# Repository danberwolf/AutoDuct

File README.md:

# AutoDuct: smart motorized air duct shutter

AutoDuct is a smart DIY air duct shutter for decentralized ventilation systems in residential buildings. Its main purpose is to automatically control airflow and block outside noise using a 3D-printed shutter system. This solves the problem of unintended air flow into the apartment during cold and windy days to increase comfort, maintain energy efficiency and reduce expenses for heating.
The integrated electronics of the air duct shutter assembly also gives full control of the ventilation system’s fan to enable features like flexible ventilation schedules and automatic humidity control. The Bluetooth low energy interface lets you control and configure the system via a mobile app. Multiple ventilation units can also be integrated into Apple HomeKit via a simple ESP32-powered BLE-to-Wifi-bridge.

# Mechanical Assembly

At the heart of this device is a mostly 3D-printed linear actuator which is used to open and close a shutter disc to prevent unwanted airflow. The 3D-printed leadscrew of the actuator is directly attached to a small brushed DC motor with an integrated gearbox.

Integrated into the encapsulated actuator unit two hall effect switches on a separate ring-shaped PCB are used to detect the end stop positions (open/close) of the shutter mechanism in combination with tiny magnets. The axial position of these magnets can be adjusted to compensate for mechanical tolerances in the assembly.

Note: the actuator unit does not use any additional (ball) bearings to keep the BOM simple and material cost low. Axial and radial forces are solely absorbed by the 3D-printed linear guides and the integrated bearings of the geared motor. This could potentially reduce longevity of the assembly but has not been an issue while testing multiple units over more than a year now. Use of silicone grease is highly recommended.

# Electronics

The electronics are based around a Microchip 32-bit microcontroller (PIC32MX), which might be a little bit overpowered for this project but was available from a previous project and has a neat footprint. The +3V3 rail is generated from the +12V bus by a step-down converter. The geared DC motor is driven by a dedicated H-bridge driver IC (DRV8801).

Behind the front cover of the assembly another small PCB is hidden. This PCB contains the Bluetooth low energy module (HM-17), a serial EEPROM, a real time clock (RTC) IC and a humidity and temperature sensor. User feedback is given via a white LED which shines through the 3D-printed enclosure and has brightness control via PWM.

# Firmware

The main processor of the device (PIC32MX150F128B) runs a super simple multitasking OS which takes care of these main tasks:

* monitoring of fan control PWM signal from the stock ventilation system control bus
* reading of temperature / humidity from SHT31 sensor
* generating the PWM control signal for connected fan
* motor control including end stop detection
* handle the BLE communication when the system is connected to the mobile app 

Depending on the selected operating mode, the device will perform the following actions:

* opening / closing the valve based on the detected fan control PWM signal
* automatically activating the fan based on schedule events or humidity thresholds
* react to remote control commands issued via the mobile app / BLE connection 

A custom bootloader was developed which enables over-the-air firmware updates via the Bluetooth low energy interface. 

# Project Video

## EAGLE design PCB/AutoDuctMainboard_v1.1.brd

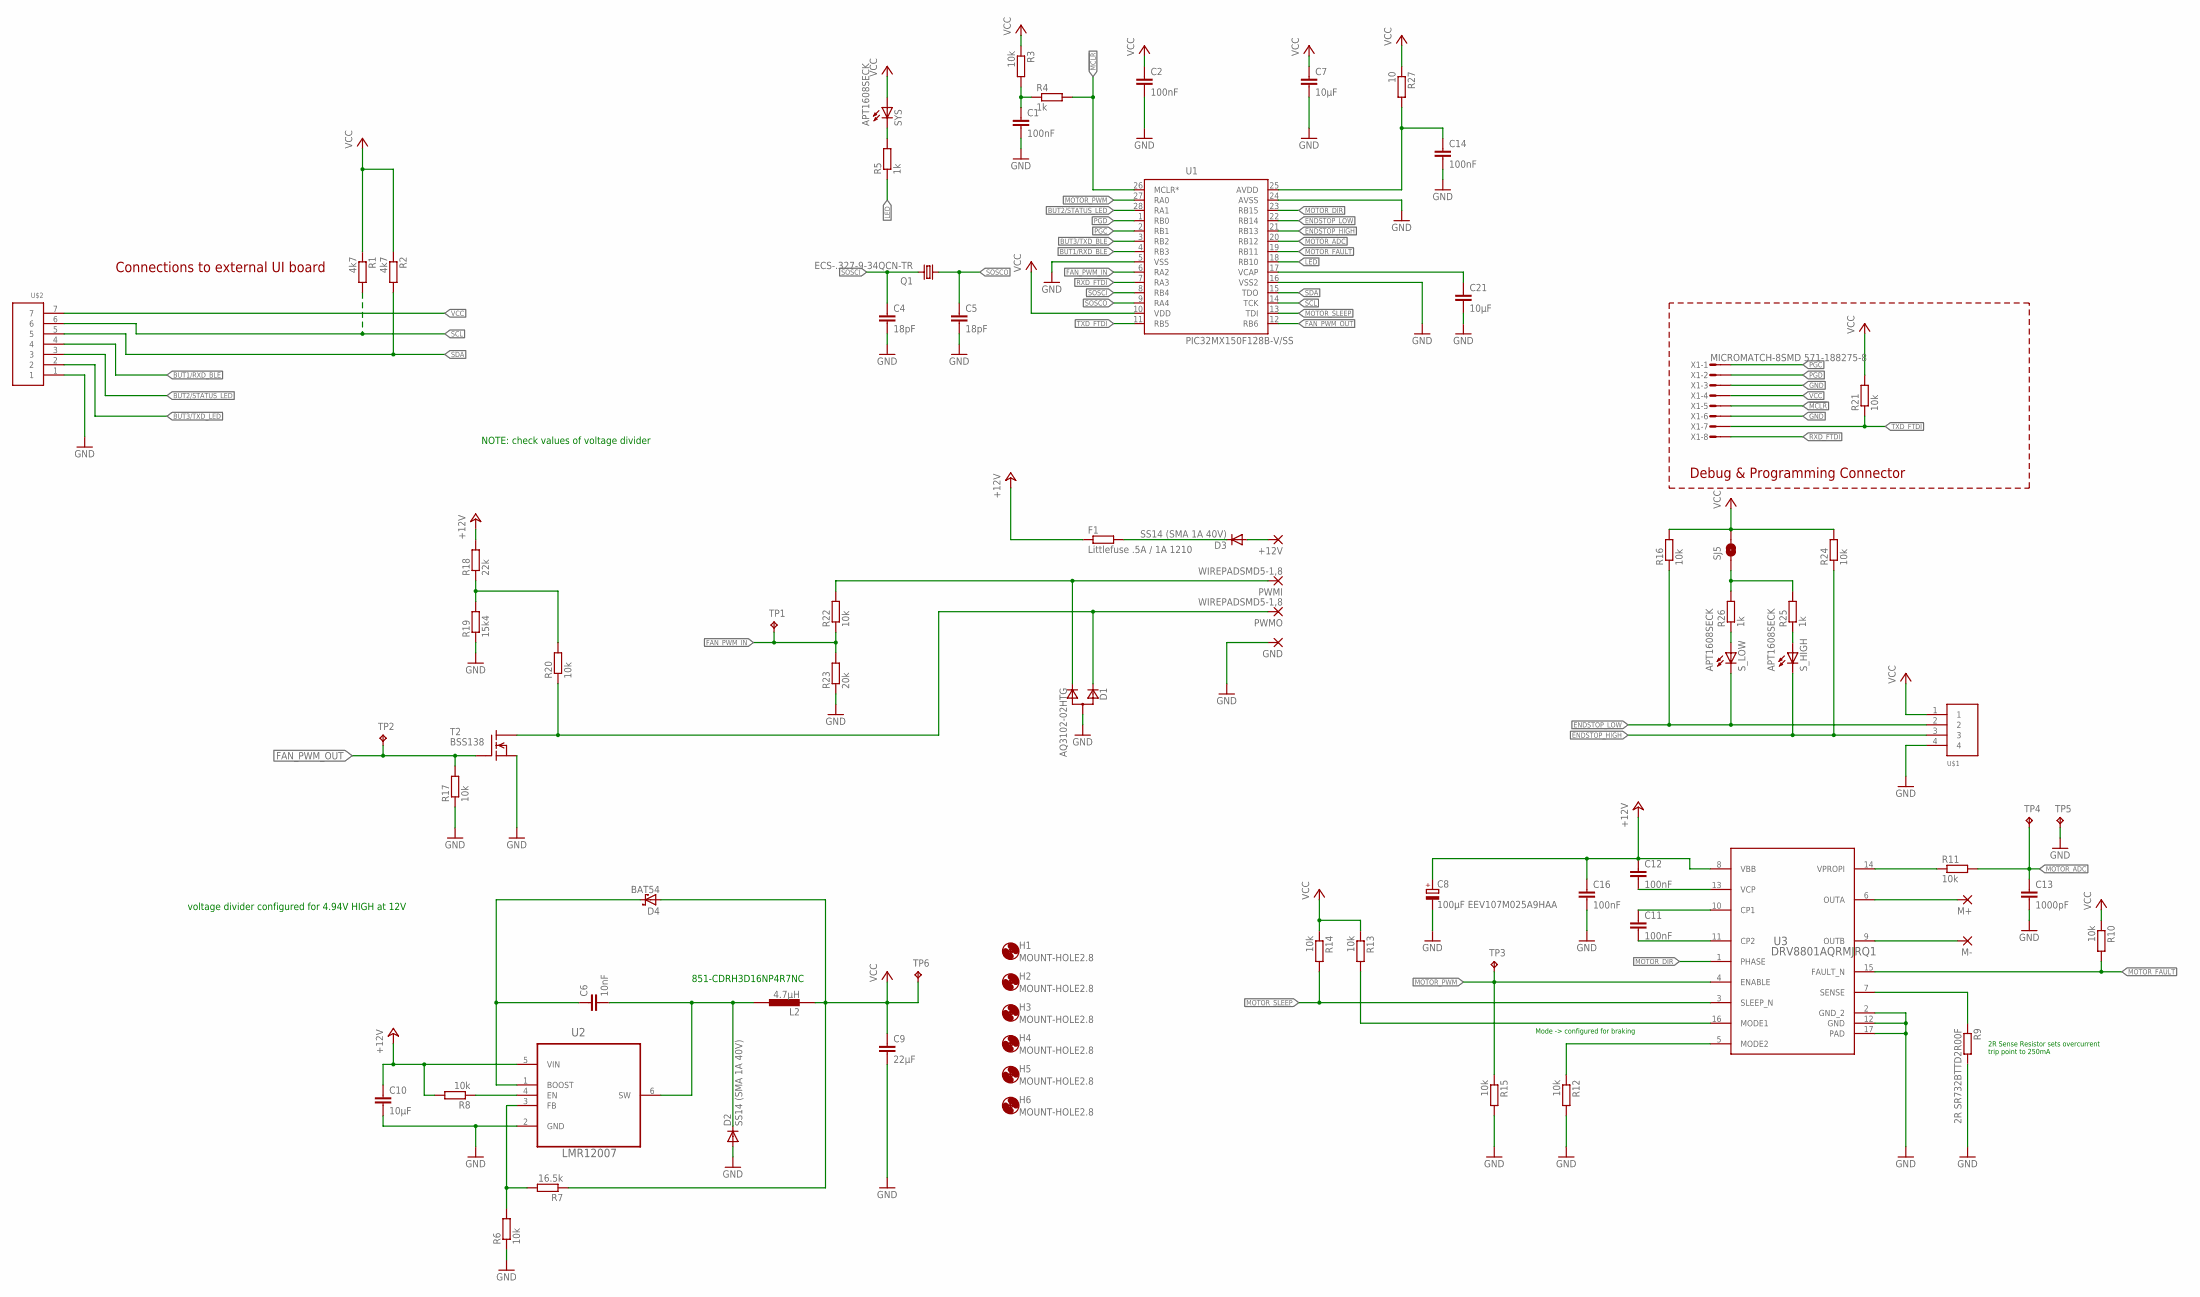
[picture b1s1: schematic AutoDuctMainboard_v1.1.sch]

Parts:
+12V: SMD5; SMD2,54-5,08
C1, C2, C11, C12, C14: 100nF; C0402
C4, C5: 18pF; C0603K
C6: 10nF; C0603K
C7, C21: 10µF; C0603K
C8: 100µF EEV107M025A9HAA; 153CLV-0605
C9: 22µF; C0805K
C10: 10µF; C1206K
C13: 1000pF; C0603K
C16: 100nF; C0603K
D1: AQ3102-02HTG; SOT323
D2, D3: SS14 (SMA 1A 40V); DO214AC
D4: BAT54; SOT23
F1: Littlefuse .5A / 1A 1210; R1210
GND: SMD5; SMD2,54-5,08
H1, H2, H3, H4, H5, H6: MOUNT-HOLE2.8; 2,8
L2: 4.7µH; CDRH3D16; MOUSER CDRH3D16/LDNP-4R7NC
M+: SMD5; SMD2,54-5,08
M-: SMD5; SMD2,54-5,08
PWMI: WIREPADSMD5-1,8; 5-1,8
PWMO: WIREPADSMD5-1,8; 5-1,8
Q1: ECS-.327-9-34QCN-TR; 3.2X1.5
R1, R2: 4k7; R0603
R3, R6, R8, R10, R11, R12, R13, R14, R15, R16, R17, R20, R21, R22, R24: 10k; R0603
R4, R5, R25, R26: 1k; R0603
R7: 16.5k; R0603
R9: 2R SR732BTTD2R00F; R1206
R18: 22k; R0603
R19: 15k4; R0603
R23: 20k; R0603
R27: 10; R0603
SJ5: RXLED; SJ_2S-NO
SYS: APT1608SECK; CHIPLED_0603
S_HIGH: APT1608SECK; CHIPLED_0603
S_LOW: APT1608SECK; CHIPLED_0603
T2: BSS138; SOT23
TP1, TP2, TP3, TP6: TPTP13R; TP13R
TP4: TPTP09R; TP09R
TP5: TPTP12SQ; TP12SQ
U1: PIC32MX150F128B-V/SS; QFN65P600X600X100-29N
U2: LMR12007; SOT95P285X100-6N
U3: DRV8801AQRMJRQ1; RMJ0016A
U$1: WIREPAD1X4
U$2: WIREPAD1X7
X1: MICROMATCH-8SMD 571-188275-8; MICROMATCH-8-SMD

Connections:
!MCLR: R4.2, U1.26 (MCLR*), X1.5
+12V: C8.+, C10.1, C12.1, C16.1, F1.1, R8.2, R18.2, U2.5 (VIN), U3.8 (VBB)
BUT1/RXD_BLE: U1.4 (RB3), U$2.4
BUT2/STATUS_LED: U1.28 (RA1), U$2.3
BUT3/TXD_BLE: U1.3 (RB2)
BUT3/TXD_LED: U$2.2
ENDSTOP_HIGH: R24.1, S_HIGH.C, U1.21 (RB13), U$1.3
ENDSTOP_LOW: R16.1, S_LOW.C, U1.22 (RB14), U$1.2
FAN_PWM_IN: R22.1, R23.2, TP1.TP, U1.6 (RA2)
FAN_PWM_IN_RAW: D1.3 (C2), PWMI.1, R22.2
FAN_PWM_OUT: R17.2, T2.1 (G), TP2.TP, U1.12 (RB6)
FAN_PWM_OUT_SHIFTED: D1.2 (C1), PWMO.1, R20.1, T2.3 (D)
GND: C1.2, C2.2, C4.2, C5.2, C7.2, C8.-, C9.2, C10.2, C13.2, C14.2, C16.2, C21.2, D1.1 (A), D2.A, GND.1, R6.1, R9.2, R12.2, R15.2, R17.1, R19.1, R23.1, T2.2 (S), TP5.TP, U1.5 (VSS), U1.16 (VSS2), U1.24 (AVSS), U2.2 (GND), U3.2 (GND_2), U3.12 (GND), U3.17 (PAD), U$1.4, U$2.1, X1.3, X1.6
LED: R5.1, U1.18 (RB10)
MOTOR+: M+.1, U3.6 (OUTA)
MOTOR-: M-.1, U3.9 (OUTB)
MOTOR_ADC: C13.1, R11.2, TP4.TP, U1.20 (RB12)
MOTOR_DIR: U1.23 (RB15), U3.1 (PHASE)
MOTOR_FAULT: R10.2, U1.19 (RB11), U3.15 (FAULT_N)
MOTOR_PWM: R15.1, TP3.TP, U1.27 (RA0), U3.4 (ENABLE)
MOTOR_SLEEP: R14.2, U1.13 (TDI), U3.3 (SLEEP_N)
unnamed: R5.2, SYS.C
unnamed: C1.1, R3.2, R4.1
unnamed: R8.1, U2.4 (EN)
unnamed: C11.1, U3.10 (CP1)
unnamed: +12V.1, D3.A
unnamed: C11.2, U3.11 (CP2)
unnamed: C6.1, D4.3 (C), U2.1 (BOOST)
unnamed: C12.2, U3.13 (VCP)
unnamed: R6.2, R7.2, U2.3 (FB)
unnamed: C6.2, D2.C, L2.2, U2.6 (SW)
unnamed: R13.2, U3.16 (MODE1)
unnamed: R12.1, U3.5 (MODE2)
unnamed: R25.2, R26.2, SJ5.1
unnamed: R9.1, U3.7 (SENSE)
unnamed: R26.1, S_LOW.A
unnamed: D3.C, F1.2
unnamed: R18.1, R19.2, R20.2
unnamed: R11.1, U3.14 (VPROPI)
unnamed: R25.1, S_HIGH.A
unnamed: C14.1, R27.2, U1.25 (AVDD)
PGC: U1.2 (RB1), X1.1
PGD: U1.1 (RB0), X1.2
RXD_FTDI: U1.7 (RA3), X1.8
SCL: R1.2, U1.14 (TCK), U$2.6
SDA: R2.2, U1.15 (TDO), U$2.5
SOSCI: C4.1, Q1.2, U1.8 (RB4)
SOSCO: C5.1, Q1.1, U1.9 (RA4)
TXD_FTDI: R21.1, U1.11 (RB5), X1.7
VCAP: C21.1, U1.17 (VCAP)
VCC: C2.1, C7.1, C9.1, D4.1 (A), L2.1, R1.1, R2.1, R3.1, R7.1, R10.1, R13.1, R14.1, R16.2, R21.2, R24.2, R27.1, SJ5.2, SYS.A, TP6.TP, U1.10 (VDD), U$1.1, U$2.7, X1.4

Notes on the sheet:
Connections to external UI board
Debug & Programming Connector
851-CDRH3D16NP4R7NC
2R Sense Resistor sets overcurrent trip point to 250mA
Mode -> configured for braking
voltage divider configured for 4.94V HIGH at 12V
NOTE: check values of voltage divider

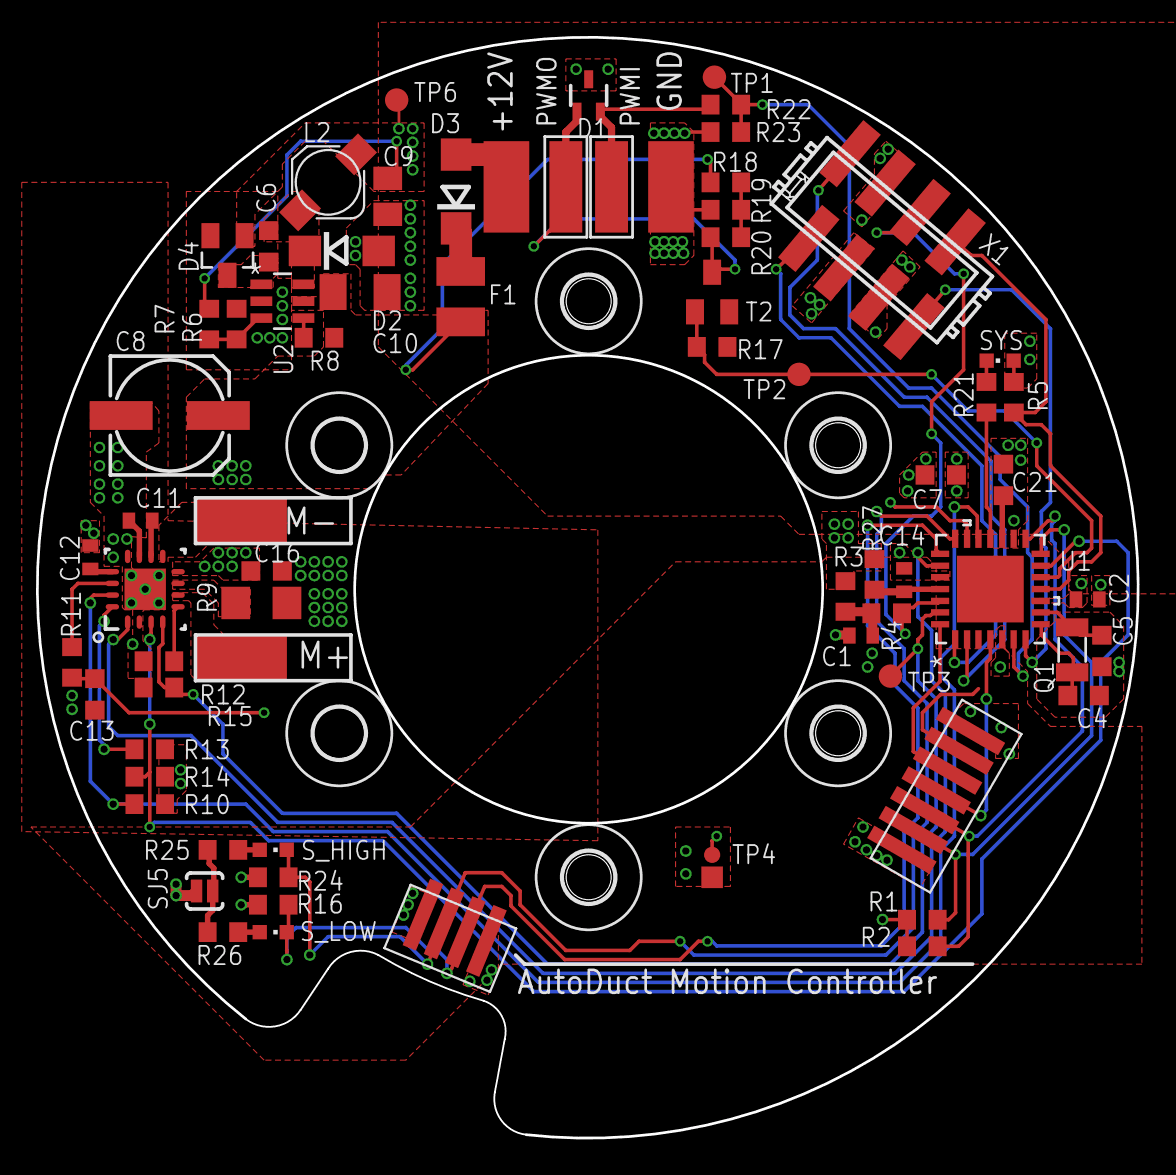
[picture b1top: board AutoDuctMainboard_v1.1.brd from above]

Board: 4 copper layers, 61.2 x 61.1 mm, 78 parts (0 on the bottom side), 49 nets.

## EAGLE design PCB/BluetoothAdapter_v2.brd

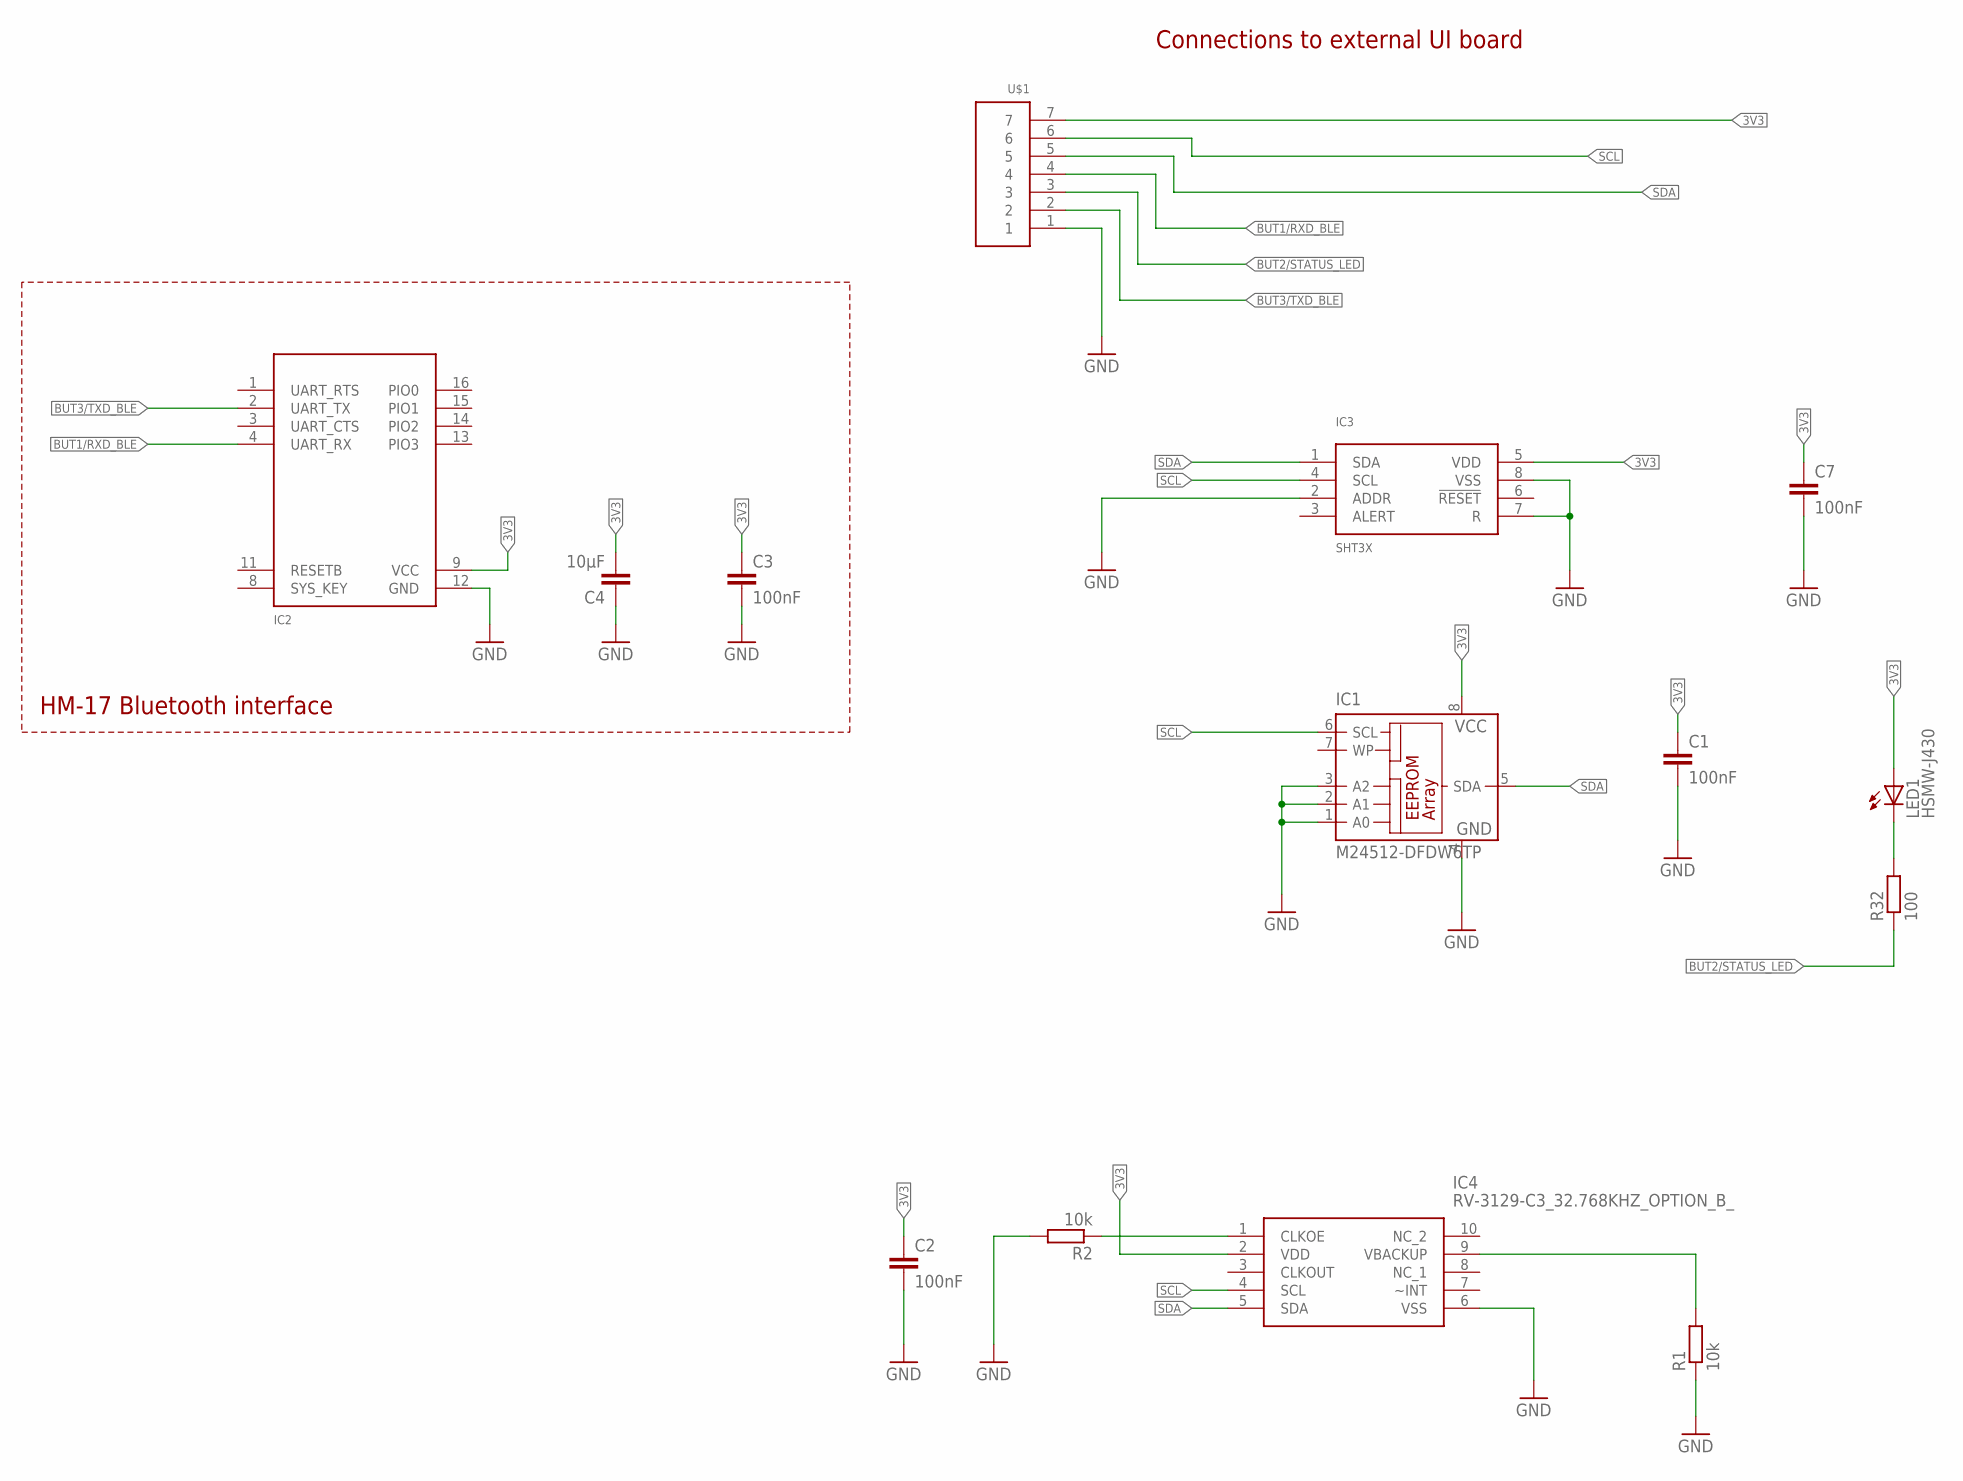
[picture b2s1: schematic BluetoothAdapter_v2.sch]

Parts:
C1, C2, C3, C7: 100nF; C0402
C4: 10µF; C0805K
IC1: M24512-DFDW6TP; TSSOP8
IC2: HM17
IC3: SHT3X; TDFN8-2.5X2.5MM
IC4: RV-3129-C3_32.768KHZ_OPTION_B_; RV3129C3
LED1: HSMW-J430; 1206
R1, R2: 10k; R0603
R32: 100; R0603
U$1: WIREPAD1X7

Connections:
3V3: C1.1, C2.1, C3.1, C4.2, C7.1, IC1.8 (VCC), IC2.9 (VCC), IC3.5 (VDD), IC4.2 (VDD), LED1.A, U$1.7
BUT1/RXD_BLE: IC2.4 (UART_RX), U$1.4
BUT2/STATUS_LED: R32.1, U$1.3
BUT3/TXD_BLE: IC2.2 (UART_TX), U$1.2
GND: C1.2, C2.2, C3.2, C4.1, C7.2, IC1.1 (A0), IC1.2 (A1), IC1.3 (A2), IC1.4 (GND), IC2.12 (GND), IC3.2 (ADDR), IC3.7 (R), IC3.8 (VSS), IC4.6 (VSS), R1.1, R2.2, U$1.1
unnamed: IC4.9 (VBACKUP), R1.2
unnamed: LED1.C, R32.2
unnamed: IC4.1 (CLKOE), R2.1
SCL: IC1.6 (SCL), IC3.4 (SCL), IC4.4 (SCL), U$1.6
SDA: IC1.5 (SDA), IC3.1 (SDA), IC4.5 (SDA), U$1.5

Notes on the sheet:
HM-17 Bluetooth interface
Connections to external UI board

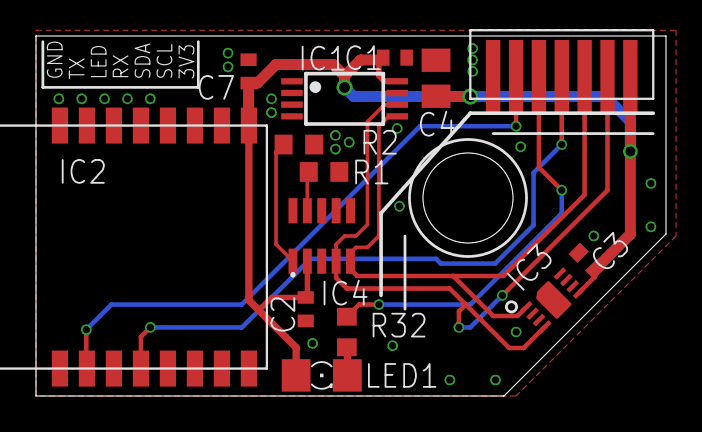
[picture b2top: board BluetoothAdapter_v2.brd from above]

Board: 2 copper layers, 35.0 x 20.0 mm, 14 parts (0 on the bottom side), 10 nets.

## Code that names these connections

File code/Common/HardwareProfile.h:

// AutoDuct Hardware definition file
// (C) 2023-09-09 by Daniel Porzig

#ifndef HARDWARE_PROFILE_H
#define HARDWARE_PROFILE_H


#include "Compiler.h"

   /** CPU Clock Speed Assignment *************************************/
    
	#define GetSystemClock()		(40000000ul)      // Hz
//	#define GetSystemClock()		(48000000ul)      // Hz
	#define GetInstructionClock()	(GetSystemClock())
	#define GetPeripheralClock()	(GetInstructionClock() / 1)	// Set your divider according to your Peripheral Bus Frequency configuration fuse setting



// ====================================================
//   Hardware mappings
// ====================================================

// BDC Motor Driver
#define MOTOR_DIR_TRIS      (TRISBbits.TRISB15)
#define MOTOR_DIR           (LATBbits.LATB15)

#define MOTOR_PWM_TRIS      (TRISAbits.TRISA0)
#define MOTOR_PWM           (LATAbits.LATA0)


#define MOTOR_SLEEP_TRIS    (TRISBbits.TRISB7)
#define MOTOR_SLEEP         (LATBbits.LATB7)

#define MOTOR_FAULT_TRIS    (TRISBbits.TRISB11)
#define MOTOR_FAULT         (LATBbits.LATB11)

#define MOTOR_ADC_TRIS      (TRISBbits.TRISB12)

// % LED INDICATORS										
#define SYSLED_TRIS         (TRISBbits.TRISB10)
#define SYSLED              (LATBbits.LATB10)

#define STATLED_TRIS         (TRISAbits.TRISA1)
#define STATLED              (LATAbits.LATA1)


//UART 2   - DEBUG
#define 	RX_CON_TRIS		(TRISBbits.TRISB5)      // input (RX)
#define 	TX_CON_TRIS		(TRISAbits.TRISA3)      // output (TX)

//UART 1   - HM-17
#define 	RX_BLE_TRIS		(TRISBbits.TRISB2)      // input (RX)
#define 	TX_BLE_TRIS		(TRISBbits.TRISB3)      // output (TX)


// PWM in/out
#define 	FAN_PWM_IN_TRIS		(TRISAbits.TRISA2)
#define 	FAN_PWM_OUT_TRIS	(TRISBbits.TRISB6)
#define 	FAN_PWM_OUT_ODC     (ODCBbits.ODCB6)      // open drain config


// user buttons
#define 	BUTTON1_TRIS		(TRISBbits.TRISB3)
#define 	BUTTON1             (PORTBbits.RB3)
        
#define 	BUTTON2_TRIS		(TRISAbits.TRISA1)
#define 	BUTTON2             (PORTAbits.RA1)

#define 	BUTTON3_TRIS		(TRISBbits.TRISB2)
#define 	BUTTON3             (PORTBbits.RB2)

// end stop sensors
#define 	ENDSTOP_LOW_TRIS		(TRISBbits.TRISB14)
#define 	ENDSTOP_LOW             (PORTBbits.RB14)
        
#define 	ENDSTOP_HIGH_TRIS		(TRISBbits.TRISB13)
#define 	ENDSTOP_HIGH            (PORTBbits.RB13)

#define BAUDRATE_UART2      115200UL
//// for PBCLOCK 40MHz
#define BRG_DIV_UART2           4   // this is NOT the baud rate register value!
#define BRGH_UART2              1

#define BAUDRATE_UART1      9600UL
//// for PBCLOCK 40MHz
#define BRG_DIV_UART1           16   // this is NOT the baud rate register value!
#define BRGH_UART1              0


//// for PBCLOCK 48MHz
//#define BRG_DIV_UART2           16  // this is NOT the baud rate register value!    
//#define BRGH_UART2               0


#define DEBUG_puts      UART2PrintString




#endif // #ifndef HARDWARE_PROFILE_H

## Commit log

2023-07-17 Create CAD
2023-07-17 initial upload
2023-07-18 Animation updated
2023-09-08 PCB design files updated
2023-09-08 Gerber files added
2023-09-11 source code initial upload
2023-11-24 Update README.md
    Link to project video added
2023-11-24 link to project video added

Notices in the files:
parts and their libraries:
crystal-geyer_V1_0: Copyright: Geyer-Electronic
SparkFun-Passives: Licensing: CC v3.0 Share-Alike You are welcome to use this library for commercial purposes.
COPYRIGHT: Copyright (C) 2022 Ultra Librarian. All rights reserved.
